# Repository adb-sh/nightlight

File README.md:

# nightlight

a little wled 5x5 led matrix

- esp8266
- 5x5 ws2812b leds

## contribute

feel free to fork and open pull requests :D

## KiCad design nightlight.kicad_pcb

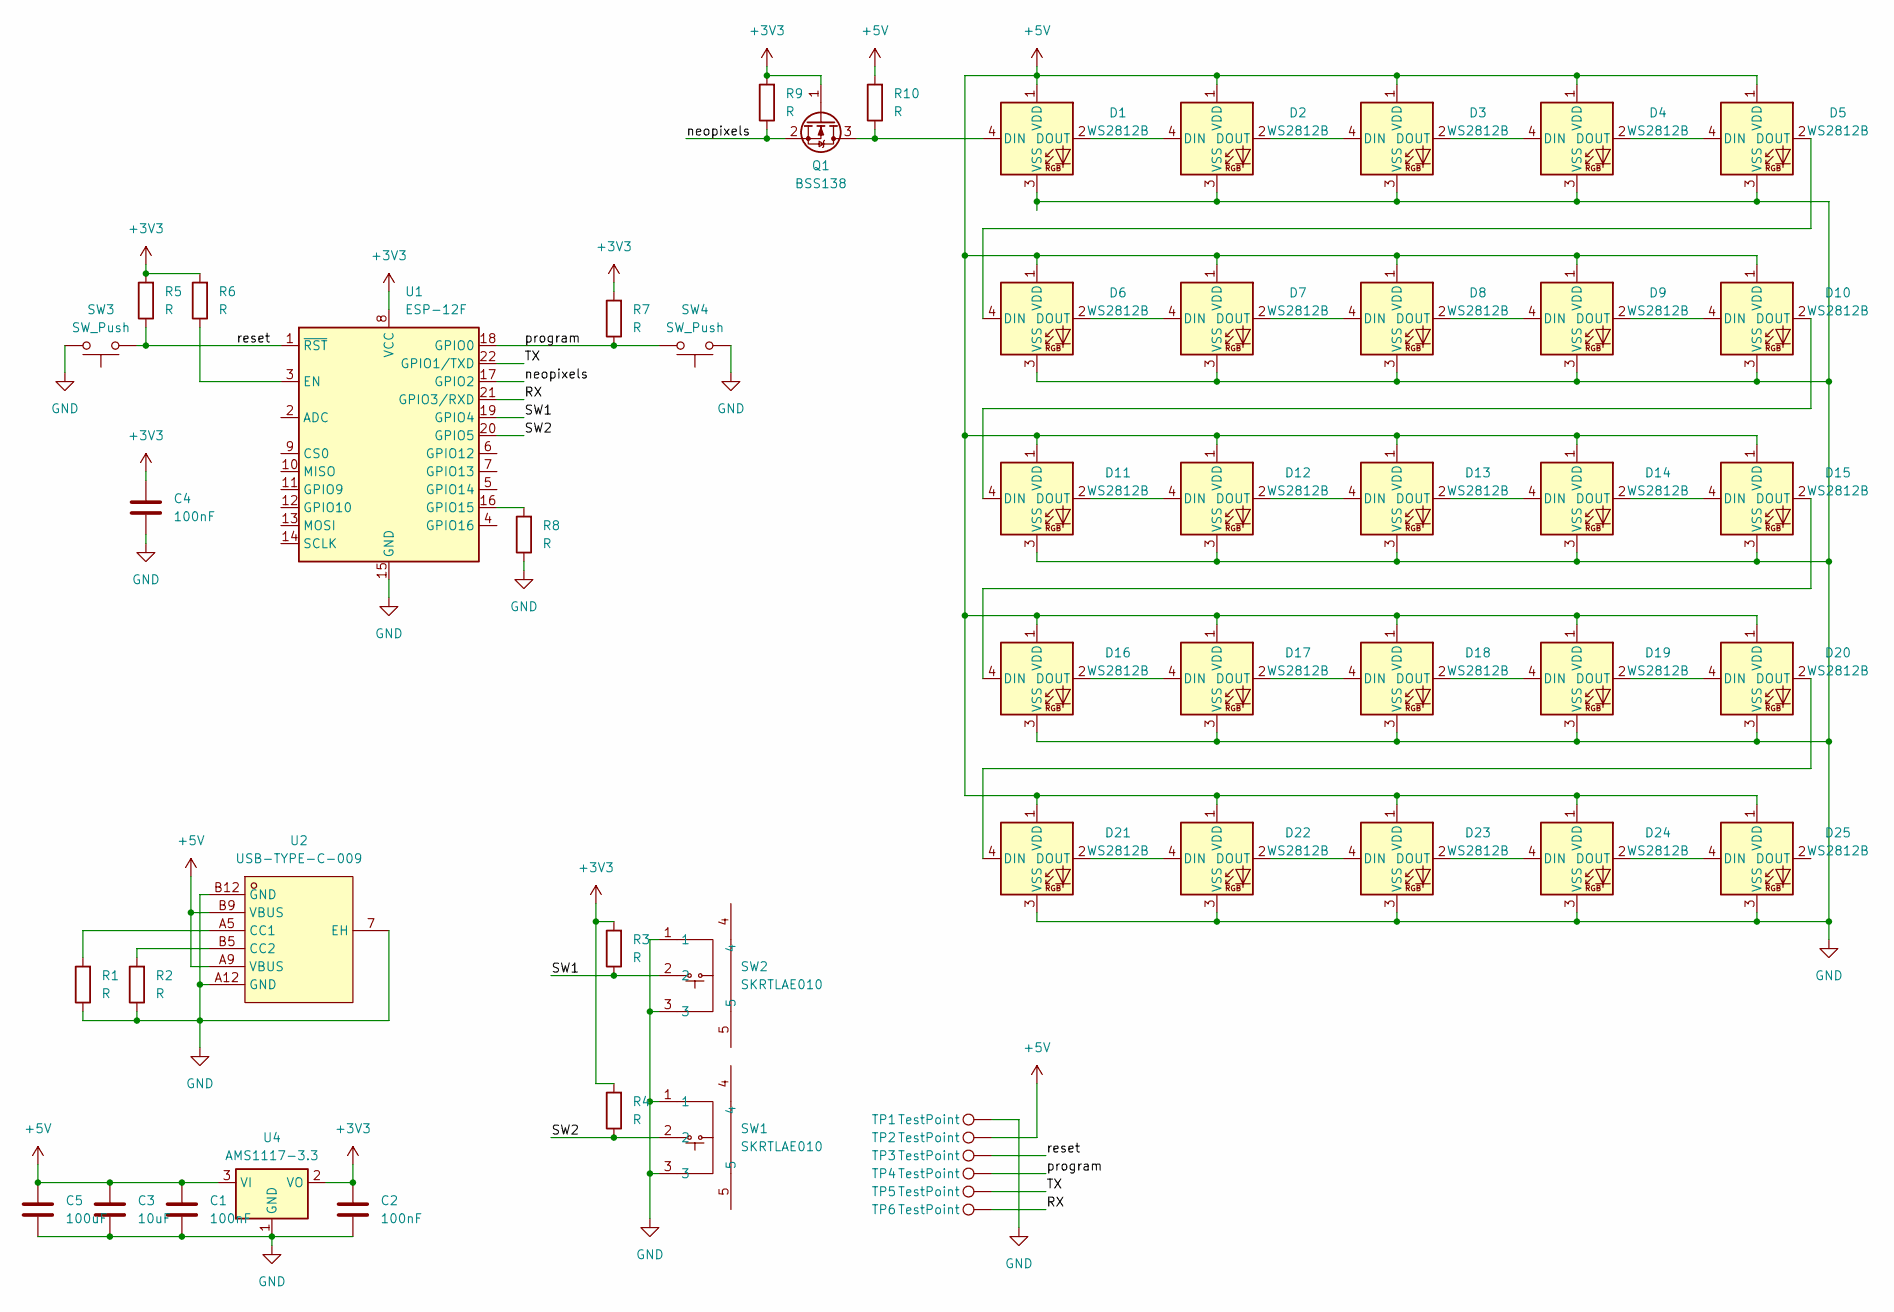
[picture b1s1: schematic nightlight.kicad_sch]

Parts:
C1, C2, C4: 100nF; C_0402_1005Metric
C3: 10uF; C_0805_2012Metric
C5: 100uF; C_1210_3225Metric
D1, D2, D3, D4, D5, D6, D7, D8, D9, D10, D11, D12, D13, D14, D15, D16, D17, D18, D19, D20, D21, D22, D23, D24, D25: WS2812B; LED_WS2812B_PLCC4_5.0x5.0mm_P3.2mm
Q1: BSS138; SOT-23
R1, R2, R3, R4, R5, R6, R7, R8, R9, R10: R; R_0603_1608Metric
SW1, SW2: SKRTLAE010; KEY-SMD_SKRTLAE010; LCSC Part C110293
SW3, SW4: SW_Push; SW-SMD_L3.9-W3.0-P4.45
TP1, TP2, TP3, TP4, TP5, TP6: TestPoint; TestPoint_Pad_D1.5mm
U1: ESP-12F; ESP-12E
U2: USB-TYPE-C-009; TYPE-C-SMD_TYPE-C-6P; LCSC Part C2927029
U4: AMS1117-3.3; SOT-223-3_TabPin2

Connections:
+3V3: C2.1, C4.1, Q1.1 (G), R3.2, R4.2, R5.2, R6.2, R7.2, R9.2, U1.8 (VCC), U4.2 (VO)
+5V: C1.1, C3.1, C5.1, D1.1 (VDD), D2.1 (VDD), D3.1 (VDD), D4.1 (VDD), D5.1 (VDD), D6.1 (VDD), D7.1 (VDD), D8.1 (VDD), D9.1 (VDD), D10.1 (VDD), D11.1 (VDD), D12.1 (VDD), D13.1 (VDD), D14.1 (VDD), D15.1 (VDD), D16.1 (VDD), D17.1 (VDD), D18.1 (VDD), D19.1 (VDD), D20.1 (VDD), D21.1 (VDD), D22.1 (VDD), D23.1 (VDD), D24.1 (VDD), D25.1 (VDD), R10.2, TP2.1, U2.A9 (VBUS), U2.B9 (VBUS), U4.3 (VI)
/RX: TP6.1, U1.21 (GPIO3/RXD)
/SW1: R3.1, SW2.2, U1.19 (GPIO4)
/SW2: R4.1, SW1.2, U1.20 (GPIO5)
/TX: TP5.1, U1.22 (GPIO1/TXD)
/neopixels: Q1.2 (S), R9.1, U1.17 (GPIO2)
/program: R7.1, SW4.2, TP4.1, U1.18 (GPIO0)
/reset: R5.1, SW3.1, TP3.1, U1.1 (~RST)
GND: C1.2, C2.2, C3.2, C4.2, C5.2, D1.3 (VSS), D2.3 (VSS), D3.3 (VSS), D4.3 (VSS), D5.3 (VSS), D6.3 (VSS), D7.3 (VSS), D8.3 (VSS), D9.3 (VSS), D10.3 (VSS), D11.3 (VSS), D12.3 (VSS), D13.3 (VSS), D14.3 (VSS), D15.3 (VSS), D16.3 (VSS), D17.3 (VSS), D18.3 (VSS), D19.3 (VSS), D20.3 (VSS), D21.3 (VSS), D22.3 (VSS), D23.3 (VSS), D24.3 (VSS), D25.3 (VSS), R1.1, R2.1, R8.1, SW1.1, SW1.3, SW2.1, SW2.3, SW3.2, SW4.1, TP1.1, U1.15 (GND), U2.7 (EH), U2.A12 (GND), U2.B12 (GND), U4.1 (GND)
unnamed: D1.4 (DIN), Q1.3 (D), R10.1
unnamed: D1.2 (DOUT), D2.4 (DIN)
unnamed: D2.2 (DOUT), D3.4 (DIN)
unnamed: D3.2 (DOUT), D4.4 (DIN)
unnamed: D4.2 (DOUT), D5.4 (DIN)
unnamed: D5.2 (DOUT), D6.4 (DIN)
unnamed: D6.2 (DOUT), D7.4 (DIN)
unnamed: D7.2 (DOUT), D8.4 (DIN)
unnamed: D8.2 (DOUT), D9.4 (DIN)
unnamed: D9.2 (DOUT), D10.4 (DIN)
unnamed: D10.2 (DOUT), D11.4 (DIN)
unnamed: D11.2 (DOUT), D12.4 (DIN)
unnamed: D12.2 (DOUT), D13.4 (DIN)
unnamed: D13.2 (DOUT), D14.4 (DIN)
unnamed: D14.2 (DOUT), D15.4 (DIN)
unnamed: D15.2 (DOUT), D16.4 (DIN)
unnamed: D16.2 (DOUT), D17.4 (DIN)
unnamed: D17.2 (DOUT), D18.4 (DIN)
unnamed: D18.2 (DOUT), D19.4 (DIN)
unnamed: D19.2 (DOUT), D20.4 (DIN)
unnamed: D20.2 (DOUT), D21.4 (DIN)
unnamed: D21.2 (DOUT), D22.4 (DIN)
unnamed: D22.2 (DOUT), D23.4 (DIN)
unnamed: D23.2 (DOUT), D24.4 (DIN)
unnamed: D24.2 (DOUT), D25.4 (DIN)
unnamed: R6.1, U1.3 (EN)
unnamed: R8.2, U1.16 (GPIO15)
unnamed: R1.2, U2.A5 (CC1)
unnamed: R2.2, U2.B5 (CC2)

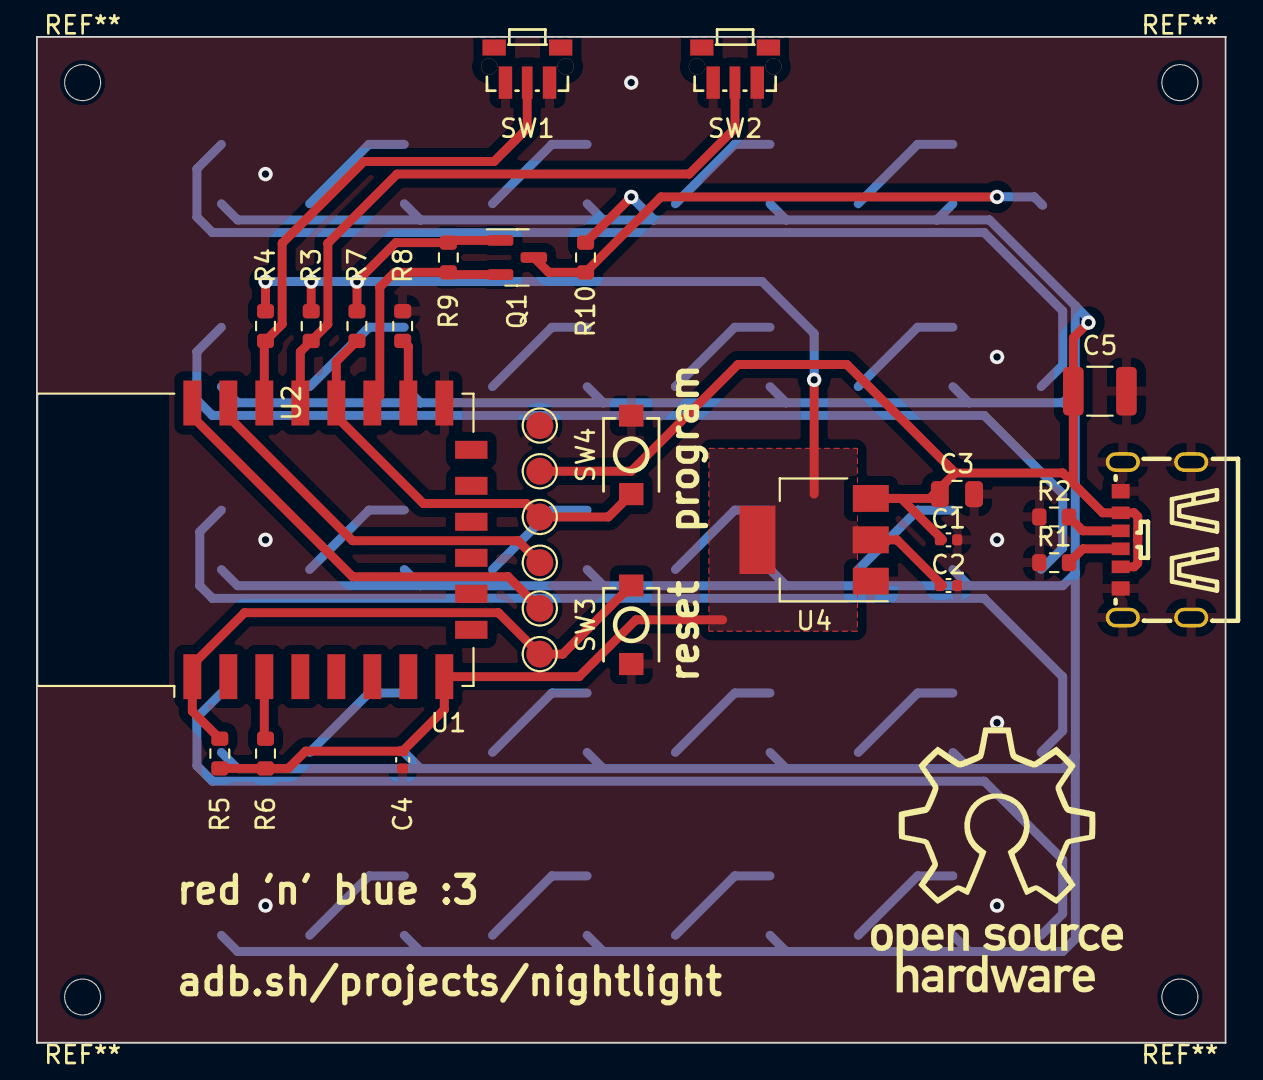
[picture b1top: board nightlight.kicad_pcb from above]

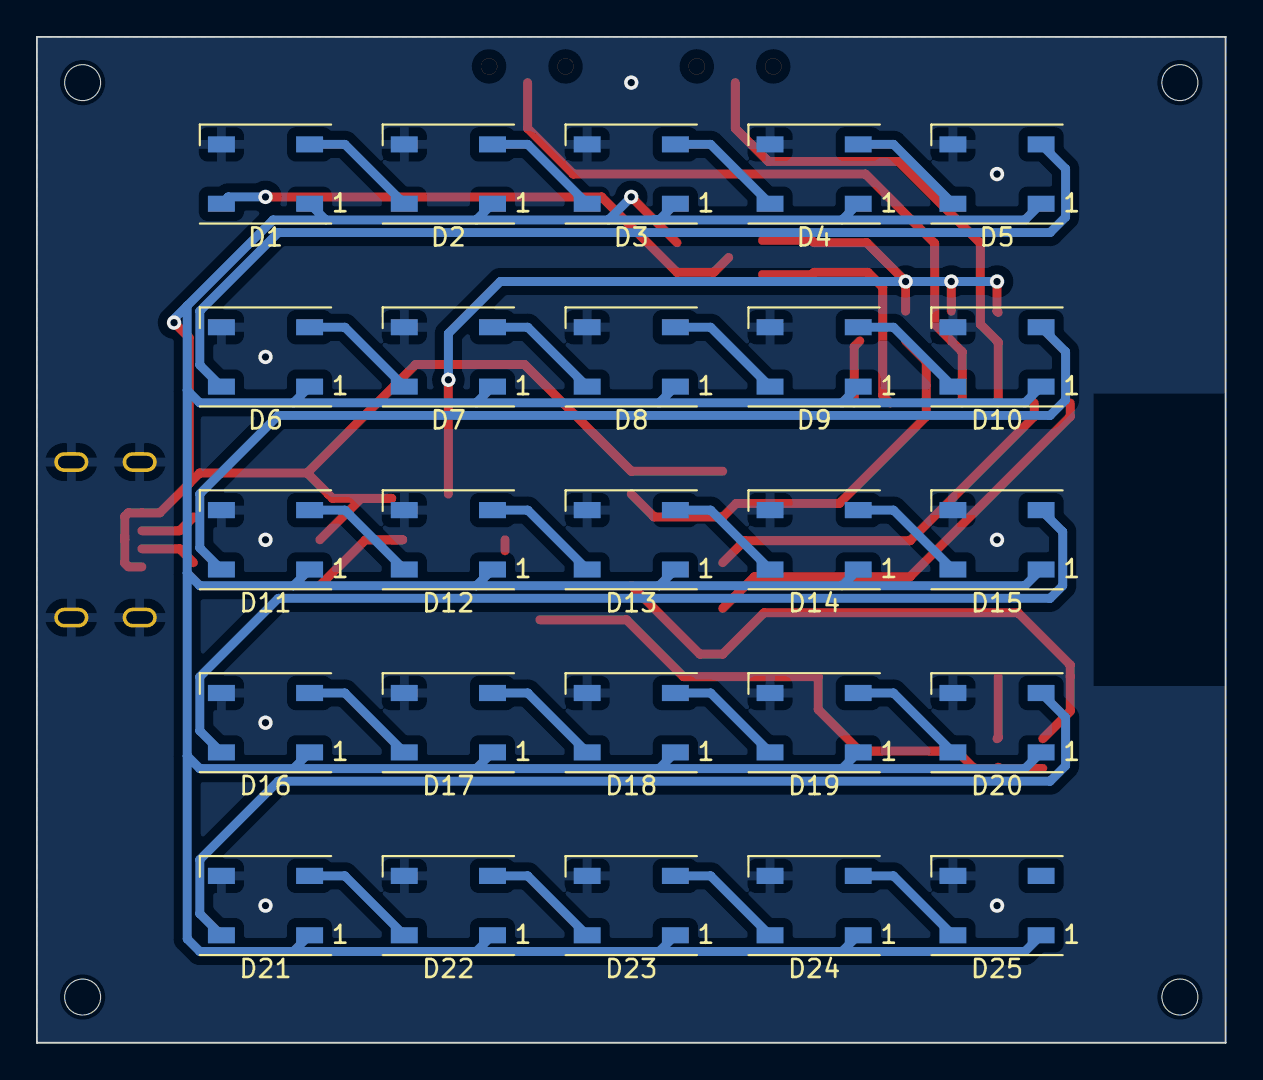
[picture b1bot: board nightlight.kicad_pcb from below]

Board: 2 copper layers, 66.0 x 55.9 mm, 54 parts (25 on the bottom side), 39 nets.

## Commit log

2024-03-23 init
2024-03-23 Rearrange front side Add images, readme
2024-03-23 Create LICENSE
2024-03-23 flip gnd and 5v on flash pins
2024-03-28 Add C4, C5 Remove J1 Add pads for flashing Add level shifter
2024-04-10 Add images
